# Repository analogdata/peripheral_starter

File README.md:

# AD - Peripheral Starter Board

A versatile peripheral development board designed for microcontroller projects, providing commonly used input/output components for rapid prototyping and learning.

**Status:** Design in Progress
**Version:** v1
**Date:** 2026-02-10
**EDA Tool:** KiCad 9.0

## Overview

The Peripheral Starter Board is an expansion board that provides a variety of peripheral components commonly used in embedded systems development. It is designed to interface with microcontroller development boards, offering ready-to-use circuits for sensors, actuators, and user interface components.

## Features

### Input Peripherals
- **4x Push Button Switches** - Tactile switches for user input
- **Potentiometer** - Analog input for variable resistance/voltage readings
- **LDR (Light Dependent Resistor)** - Light sensing for ambient light detection

### Output Peripherals
- **4x LEDs** - Standard indicator LEDs with current limiting resistors (330 ohm)
- **WS2812B RGB LED** - Addressable RGB LED for colorful visual feedback
- **Piezo Buzzer** - Audio output with transistor driver (BC547)

### Display Interface
- **OLED SSD1306 Connector** - I2C interface for 128x64 OLED display module

### Timekeeping
- **RTC Circuit Connector** - Interface for Real-Time Clock modules

### Power Management
- **5V Input** - Main power input from controller board
- **3.3V Regulated Output** - AMS1117-3.3 linear voltage regulator
- **Power Jumper Shunt** - Selectable power source from controller

## Schematic Sections

| Section | Description |
|---------|-------------|
| LED Circuit | 4 LEDs with 330 ohm current limiting resistors |
| Switches Circuit | 4 push buttons with pull-up/pull-down configuration |
| Potentiometer Circuit | Analog voltage divider circuit |
| LDR Circuit | Light sensor with voltage divider |
| RGB (WS2812B) Circuit | Addressable LED with decoupling capacitor |
| Buzzer Circuit | Piezo buzzer with BC547 transistor driver |
| OLED SSD1306 Circuit | I2C connector for OLED display |
| RTC Circuit | Connector for RTC module interface |
| 3.3V Power Supply | AMS1117-3.3 with input/output capacitors |

## Bill of Materials (Key Components)

| Reference | Component | Value/Part |
|-----------|-----------|------------|
| U1 | Voltage Regulator | AMS1117-3.3 |
| Q1 | NPN Transistor | BC547 |
| D1-D4 | LED | Standard LED |
| D5 | RGB LED | WS2812B |
| R1-R4 | Resistor | 330 ohm |
| R12, R16 | Resistor | 4.7k ohm |
| R14 | Resistor | 10k ohm |
| C1-C8 | Capacitor | 100nF / 0.1uF |
| J1-J11 | Connectors | Pin Headers (2-6 pins) |
| - | Buzzer | Piezo Buzzer |
| - | LDR | LDR07 |
| - | Potentiometer | 10k (typical) |
| - | Switches | 4x Tactile Push Buttons |
| - | Slide Switch | SPDT Slide Switch |

## Connectors

- **J4** - 6-pin Controller Interface
- **J5, J7** - 2-pin Power/Signal Connectors
- **J10, J11** - 5-pin I2C/SPI Connectors (OLED, RTC)
- **J3, J1** - 4-pin Peripheral Connectors
- **J2** - 3-pin Buzzer/RGB Connector

## Getting Started

1. **Power Supply**: Connect 5V power through the main connector or use the power jumper to receive power from the controller board
2. **Controller Interface**: Connect to your microcontroller via the pin headers
3. **Test Components**: Use the provided test points to verify functionality

## Design Files

- `peripheral_Starter.kicad_sch` - Schematic file
- `peripheral_Starter.kicad_pcb` - PCB layout file
- `peripheral_Starter.kicad_pro` - KiCad project file
- `Peripheral_Starter_v1.pdf` - Schematic PDF export

## Requirements

- KiCad 9.0 or later to open and edit design files

## Project Structure

```
peripheral_Starter/
├── peripheral_Starter.kicad_pro    # Project file
├── peripheral_Starter.kicad_sch    # Schematic
├── peripheral_Starter.kicad_pcb    # PCB layout
├── peripheral_Starter.kicad_prl    # Local project settings
├── fp-info-cache                   # Footprint cache
├── Peripheral_Starter_v1.pdf       # Schematic export
└── peripheral_Starter-backups/     # Design backups
```

## License

This project is open source hardware.

## Author

Analog Data
Website: [https://analogdata.io](https://analogdata.io)

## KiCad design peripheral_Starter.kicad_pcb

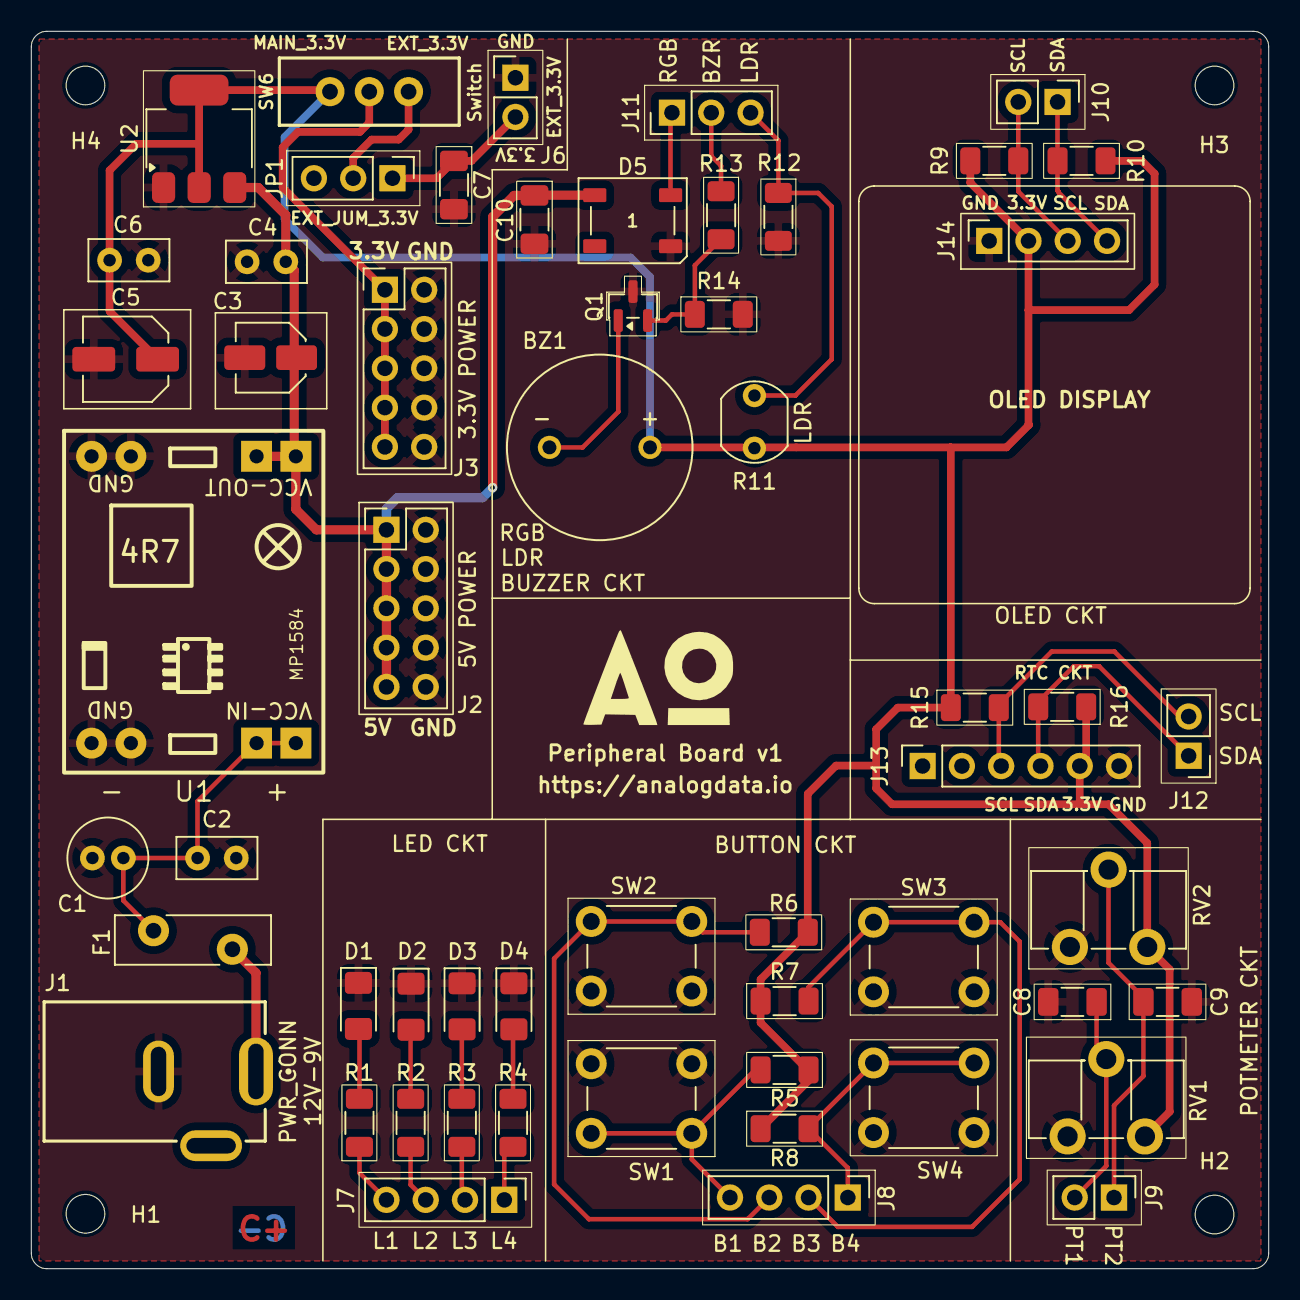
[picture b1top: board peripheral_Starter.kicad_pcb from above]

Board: 2 copper layers, 80.0 x 80.0 mm, 61 parts (1 on the bottom side), 31 nets.

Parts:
BZ1: Buzzer; BUZZ_12x8mm-1206S
C1: 47uF/25V; C_Radial_D5.0mm_H11.0mm_P2.00mm
C2, C4, C6: 0.1 uF; C_Disc_D5.0mm_W2.5mm_P2.50mm
C3: 10uF; C_Elec_4x5.4
C5: 22uF; C_Elec_5x5.4
C7, C10: 0.1 uF; C_1206_3216Metric_Pad1.33x1.80mm_HandSolder
C8, C9: 100 nF; C_1206_3216Metric_Pad1.33x1.80mm_HandSolder
D1, D2, D3, D4: LED; LED_1206_3216Metric_Pad1.42x1.75mm_HandSolder
D5: WS2812B; LED_WS2812B_PLCC4_5.0x5.0mm_P3.2mm
F1: Polyfuse; Fuse_Bourns_MF-RG400
G1: OSHW_Logo; OSHW_Logo_6mm
H1, H2, H3, H4: MountingHole; MountingHole_2.5mm
J1: Barrel_Jack; DCJack
J2: 5V_rail; PinHeader_2x05_P2.54mm_Vertical
J3: 3.3V_rail; PinHeader_2x05_P2.54mm_Vertical
J6, J9, J10, J12: Conn_01x02_Pin; PinHeader_1x02_P2.54mm_Vertical
J7, J8: Conn_01x04_Pin; PinHeader_1x04_P2.54mm_Vertical
J11: Conn_01x03_Pin; PinHeader_1x03_P2.54mm_Vertical
J13: Conn_01x06_Pin; PinSocket_1x06_P2.54mm_Vertical
J14: Conn_01x04_Pin; PinSocket_1x04_P2.54mm_Vertical
JP1: Jumper_3_Bridged12; PinHeader_1x03_P2.54mm_Vertical
Q1: BC547; SOT-23
R1, R2, R3, R4: 330; R_1206_3216Metric_Pad1.30x1.75mm_HandSolder
R5, R6, R7, R8, R12: 10k; R_1206_3216Metric_Pad1.30x1.75mm_HandSolder
R9, R10, R15, R16: 4.7k; R_1206_3216Metric_Pad1.30x1.75mm_HandSolder
R11: LDR07; R_LDR_5.1x4.3mm_P3.4mm_Vertical
R13: 1k; R_1206_3216Metric_Pad1.30x1.75mm_HandSolder
R14: 100k; R_1206_3216Metric_Pad1.30x1.75mm_HandSolder
RV1, RV2: 10k; Potentiometer_ACP_CA9-H5_Horizontal
SW1, SW2, SW3, SW4: SW_Push; SW_PUSH_6mm_H5mm
SW6: Slide Sw; Slide_SPDT_PTH_11.6x4.0mm
U1: MP1584 step down Module; MP1584 STEP DOWN MODULE - PCB
U2: AMS1117-3.3; SOT-223-3_TabPin2

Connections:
5V: C3.1, C4.1, C10.1, D5.1 (VDD), J2.1, J2.2, J2.3, J2.4, J2.5, U1.3 (VCC-out), U2.3 (VI)
+3.3V: BZ1.1 (+), C5.1, C6.1, J13.5, J14.2, R5.1, R6.1, R7.1, R8.1, R9.1, R10.1, R11.1, R15.1, R16.1, RV1.3, RV2.3, SW6.1 (A), U2.2 (VO)
+9V: F1.1, J1.1
/Sheet 1 - Power Section/3.3V Jumper: JP1.2 (C), SW6.3 (C)
/Sheet 1 - Power Section/3.3V uC: C7.1, J6.2, JP1.1 (A)
/Sheet 2 - Peripheral Circuit/SCL-OLED: J10.2, J14.3, R9.2
/Sheet 2 - Peripheral Circuit/SCL-RTC: J12.2, J13.3, R15.2
/Sheet 2 - Peripheral Circuit/SDA-OLED: J10.1, J14.4, R10.2
/Sheet 2 - Peripheral Circuit/SDA-RTC: J12.1, J13.4, R16.2
/Sheet 2 - Peripheral Circuit/Signal: J7.1, R4.1
GND: C1.2, C2.2, C3.2, C4.2, C5.2, C6.2, C7.2, C8.2, C9.2, C10.2, D1.1 (K), D2.1 (K), D3.1 (K), D4.1 (K), D5.3 (VSS), J1.2, J2.6, J2.7, J2.8, J2.9, J2.10, J3.6, J3.7, J3.8, J3.9, J3.10, J6.1, J13.6, J14.1, Q1.3 (E), R12.2, R14.2, RV1.1, RV2.1, SW1.2, SW2.2, SW3.2, SW4.2, U1.1 (GND), U1.4 (GND), U2.1 (GND)
unnamed: BZ1.2 (-), Q1.1 (C)
unnamed: D1.2 (A), R1.2
unnamed: D2.2 (A), R2.2
unnamed: D3.2 (A), R3.2
unnamed: D4.2 (A), R4.2
unnamed: D5.4 (DIN), J11.1
unnamed: J3.1, J3.2, J3.3, J3.4, J3.5, SW6.2 (B)
unnamed: J7.2, R3.1
unnamed: J7.3, R2.1
unnamed: J7.4, R1.1
unnamed: J8.1, R8.2, SW4.1
unnamed: J8.2, R7.2, SW3.1
unnamed: J8.3, R6.2, SW2.1
unnamed: J8.4, R5.2, SW1.1
unnamed: C9.1, J9.1, RV2.2
unnamed: C8.1, J9.2, RV1.2
unnamed: J11.2, R13.1
unnamed: J11.3, R11.2, R12.1
unnamed: Q1.2 (B), R13.2, R14.1
unnamed: C1.1, C2.1, F1.2, U1.2 (VCC-in)

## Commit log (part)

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2026-02-11 Power Section Added and Sheets Updated
2026-02-16 routing and gerber finished file
